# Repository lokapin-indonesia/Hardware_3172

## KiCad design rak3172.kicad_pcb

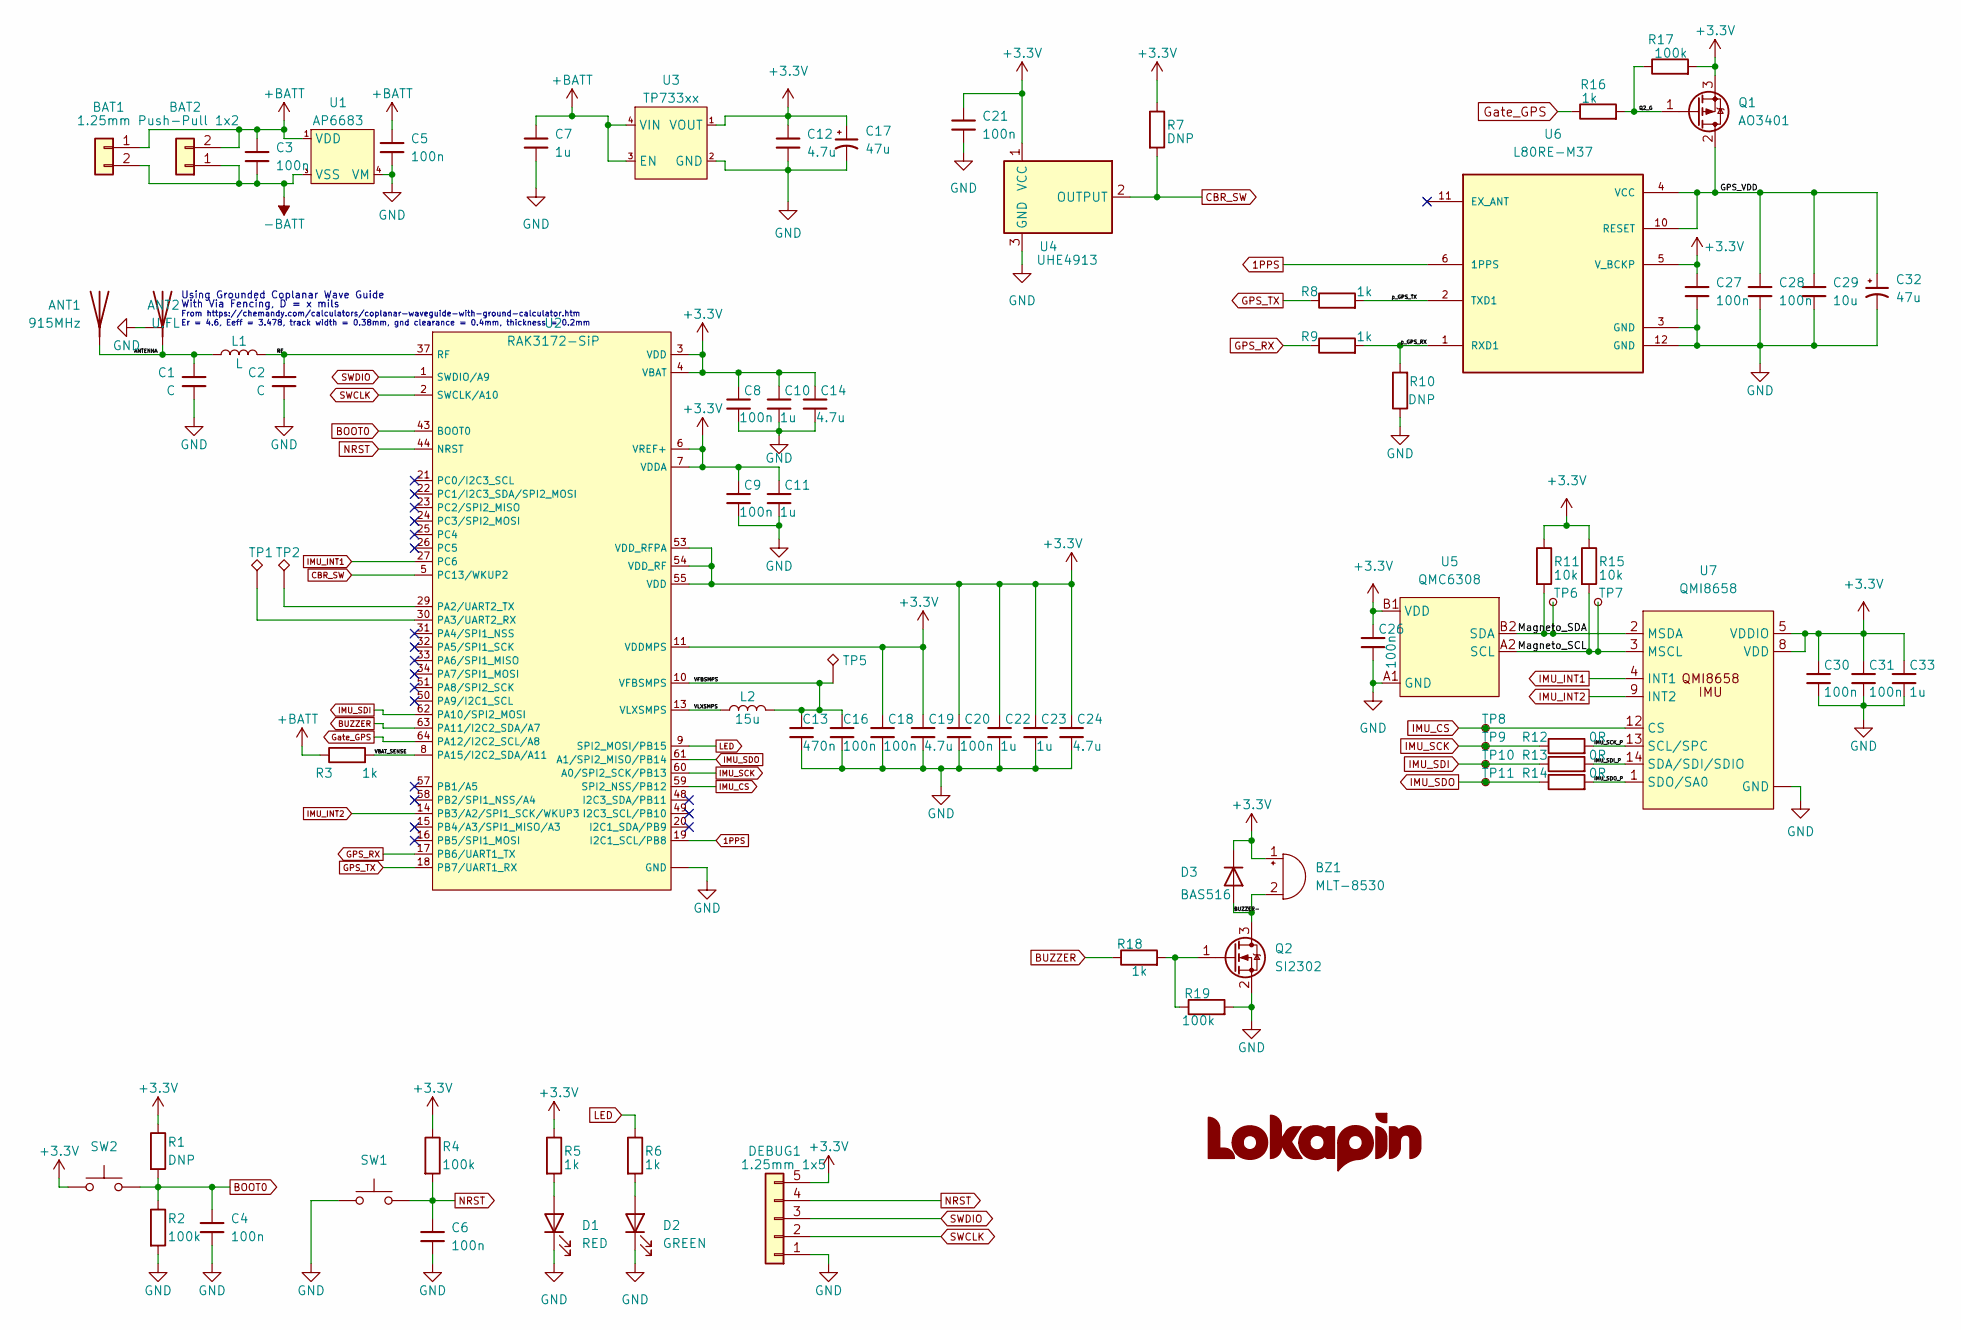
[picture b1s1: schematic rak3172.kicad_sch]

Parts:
ANT1: 915MHz; TestPoint_THTPad_D2.0mm_Drill1.0mm
ANT2: U.FL; U.FL_Hirose_U.FL-R-SMT-1_Vertical
BAT1, BAT2: 1.25mm Push-Pull 1x2; 1.25-2PWB DEALON
BZ1: MLT-8530; MagneticBuzzer_8530_SMD
C1, C2: C; C_0402_1005Metric
C3, C4, C5, C6, C8, C9, C16, C18, C20, C21, C26, C27, C28, C30, C31: 100n; C_0402_1005Metric
C7, C10, C11, C22, C23, C33: 1u; C_0402_1005Metric
C12, C14, C19, C24: 4.7u; C_0402_1005Metric
C13: 470n; C_0402_1005Metric
C17, C32: 47u; CP_EIA-3216-18_Kemet-A
C29: 10u; C_0402_1005Metric
D1: RED; LED_0603_1608Metric
D2: GREEN; LED_0603_1608Metric
D3: BAS516; D_SOD-523
DEBUG1: 1.25mm 1x5; Hirose_DF13-05P-1.25DSA_1x05_P1.25mm_Vertical
L1: L; L_0402_1005Metric
L2: 15u; L_0805_2012Metric
Q1: AO3401; SOT-23
Q2: SI2302; SOT-23
R1, R7, R10: DNP; R_0402_1005Metric
R2, R4, R17, R19: 100k; R_0402_1005Metric
R3, R5, R6, R8, R9, R16, R18: 1k; R_0402_1005Metric
R11, R15: 10k; R_0402_1005Metric
R12, R13, R14: 0R; R_0402_1005Metric
SW1, SW2: SW_Push; 5.2mm x 3.35mm Tactile Switch
TP1, TP2, TP5: TestPoint_Alt; TestPoint_Pad_D1.0mm
TP6, TP7, TP8, TP9, TP10, TP11: TestPoint_Small; TestPoint_Pad_D1.0mm
U1: AP6683; OnSemi_XDFN4-1EP_1.0x1.0mm_EP0.52x0.52mm
U2: RAK3172-SiP
U3: TP733xx; OnSemi_XDFN4-1EP_1.0x1.0mm_EP0.52x0.52mm
U4: UHE4913; SOT-23
U5: QMC6308
U6: L80RE-M37; XCVR_L80RE-M37
U7: QMI8658

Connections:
1PPS: U2.19 (I2C1_SCL/PB8), U6.6 (1PPS)
+3V3: BZ1.1 (-), C8.1, C9.1, C10.1, C11.1, C12.1, C14.1, C17.1, C18.1, C19.1, C20.1, C21.1, C22.1, C23.1, C24.1, C26.1, C27.1, C30.1, C31.1, C33.1, D3.1 (K), DEBUG1.5, Q1.3 (S), R1.1, R4.1, R5.1, R7.1, R11.1, R15.1, R17.2, SW2.1, U2.3 (VDD), U2.4 (VBAT), U2.6 (VREF+), U2.7 (VDDA), U2.11 (VDDMPS), U2.53 (VDD_RFPA), U2.54 (VDD_RF), U2.55 (VDD), U3.1 (VOUT), U4.1 (VCC), U5.B1 (VDD), U6.5 (V_BCKP), U7.5 (VDDIO), U7.8 (VDD)
+BATT: BAT1.1, BAT2.2, C3.1, C5.1, C7.1, R3.1, U1.1 (VDD), U3.3 (EN), U3.4 (VIN)
-BATT: BAT1.2, BAT2.1, C3.2, U1.2 (VSS), U1.3 (VSS)
/ANTENNA: ANT1.1 (A), ANT2.1 (A), C1.1, L1.2
/BUZZER-: BZ1.2 (+), D3.2 (A), Q2.3 (D)
/GPS_VDD: C28.1, C29.1, C32.1, Q1.2 (D), U6.4 (VCC), U6.10 (RESET)
/IMU_SCK_P: R12.2, U7.13 (SCL/SPC)
/IMU_SDI_P: R13.2, U7.14 (SDA/SDI/SDIO)
/IMU_SDO_P: R14.2, U7.1 (SDO/SA0)
/Magneto_SCL: R15.2, TP7.1, U5.A2 (SCL), U7.3 (MSCL)
/Magneto_SDA: R11.2, TP6.1, U5.B2 (SDA), U7.2 (MSDA)
/Q2_G: Q1.1 (G), R16.2, R17.1
/RF: C2.1, L1.1, U2.37 (RF)
/VBAT_SENSE: R3.2, U2.8 (PA15/I2C2_SDA/A11)
/VFBSMPS: C13.1, C16.1, L2.2, TP5.1, U2.10 (VFBSMPS)
/VLXSMPS: L2.1, U2.13 (VLXSMPS)
/p_GPS_RX: R9.2, R10.2, U6.1 (RXD1)
/p_GPS_TX: R8.2, U6.2 (TXD1)
BOOT0: C4.1, R1.2, R2.1, SW2.3, U2.43 (BOOT0)
BUZZER: R18.1, U2.63 (PA11/I2C2_SDA/A7)
CBR_SW: R7.2, U2.5 (PC13/WKUP2), U4.2 (OUTPUT)
GND: ANT2.2 (GND), C1.2, C2.2, C4.2, C5.2, C6.2, C7.2, C8.2, C9.2, C10.2, C11.2, C12.2, C13.2, C14.2, C16.2, C17.2, C18.2, C19.2, C20.2, C21.2, C22.2, C23.2, C24.2, C26.2, C27.2, C28.2, C29.2, C30.2, C31.2, C32.2, C33.2, D1.1 (K), D2.1 (K), DEBUG1.1, Q2.2 (S), R2.2, R10.1, R19.2, SW1.1, U1.4 (VM), U2.12 (GND), U2.28 (GND), U2.35 (GND), U2.36 (GND), U2.38 (GND), U2.39 (GND), U2.46 (GND), U2.47 (GND), U2.52 (GND), U2.56 (GND), U2.65 (GND), U2.66 (GND), U2.67 (GND), U2.68 (GND), U2.69 (GND), U2.70 (GND), U2.71 (GND), U2.72 (GND), U2.73 (GND), U3.2 (GND), U4.3 (GND), U5.A1 (GND), U6.3 (GND), U6.12 (GND), U7.6 (GND), U7.7 (GND)
GPS_RX: R9.1, U2.17 (PB6/UART1_TX)
GPS_TX: R8.1, U2.18 (PB7/UART1_RX)
Gate_GPS: R16.1, U2.64 (PA12/I2C2_SCL/A8)
IMU_CS: TP8.1, U2.59 (SPI2_NSS/PB12), U7.12 (CS)
IMU_INT1: U2.27 (PC6), U7.4 (INT1)
IMU_INT2: U2.14 (PB3/A2/SPI1_SCK/WKUP3), U7.9 (INT2)
IMU_SCK: R12.1, TP9.1, U2.60 (A0/SPI2_SCK/PB13)
IMU_SDI: R13.1, TP10.1, U2.62 (PA10/SPI2_MOSI)
IMU_SDO: R14.1, TP11.1, U2.61 (A1/SPI2_MISO/PB14)
LED: R6.1, U2.9 (SPI2_MOSI/PB15)
NRST: C6.1, DEBUG1.4, R4.2, SW1.3, U2.44 (NRST)
unnamed: D1.2 (A), R5.2
unnamed: D2.2 (A), R6.2
unnamed: Q2.1 (G), R18.2, R19.1
unnamed: TP1.1, U2.30 (PA3/UART2_RX)
unnamed: TP2.1, U2.29 (PA2/UART2_TX)
SWCLK: DEBUG1.2, U2.2 (SWCLK/A10)
SWDIO: DEBUG1.3, U2.1 (SWDIO/A9)

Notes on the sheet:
From https://chemandy.com/calculators/coplanar-waveguide-with-ground-calculator.htm Er = 4.6, Eeff = 3.478, track width = 0.38mm, gnd clearance = 0.4mm, thickness = 0.2mm
Using Grounded Coplanar Wave Guide
With Via Fencing, D = x mils

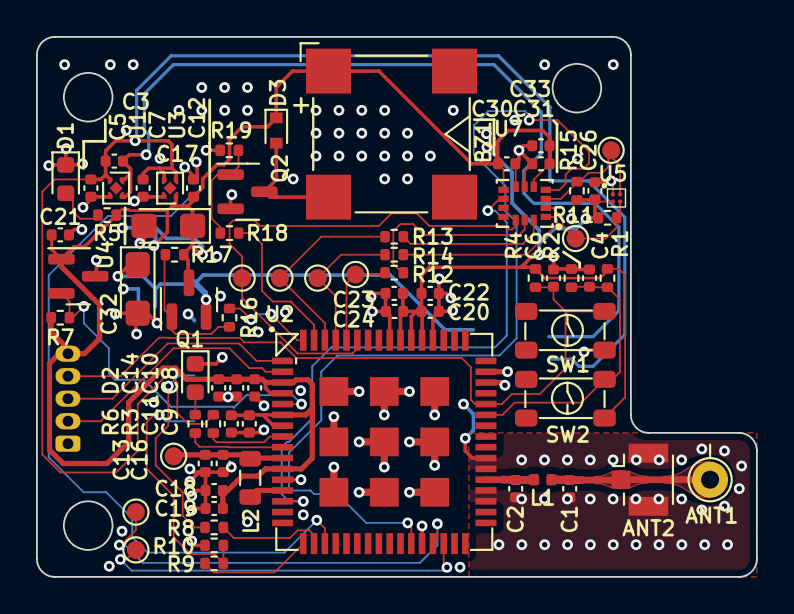
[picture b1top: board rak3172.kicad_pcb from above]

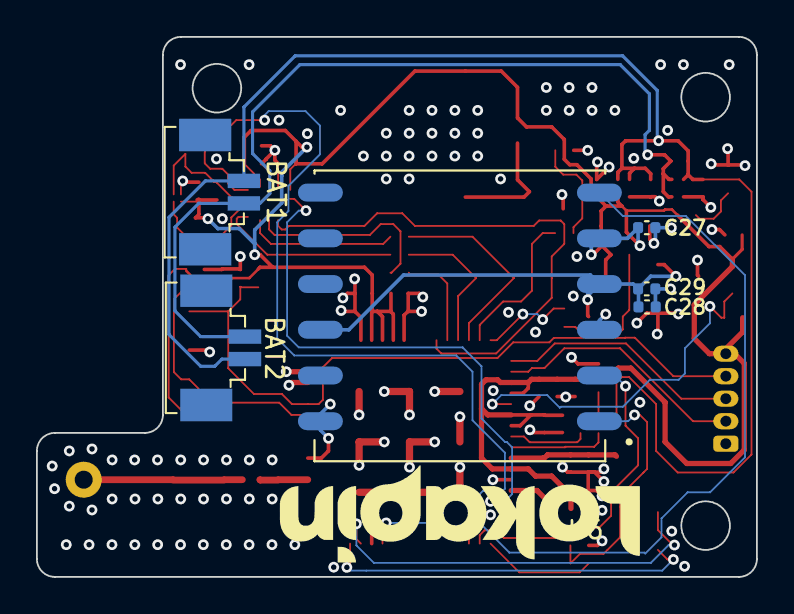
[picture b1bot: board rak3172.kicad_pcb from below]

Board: 4 copper layers, 40.0 x 30.0 mm, 81 parts (6 on the bottom side), 41 nets.

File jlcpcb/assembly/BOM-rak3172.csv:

Comment,Designator,Footprint,LCSC
100k,"R17,R19,R2,R4",R_0402_1005Metric,C106234
470n,C13,C_0402_1005Metric,C106255
47u,"C17,C32",CP_EIA-3216-18_Kemet-A,C139817
1k,"R16,R18,R3,R5,R6,R8,R9",R_0402_1005Metric,C140196
10u,C29,C_0402_1005Metric,C15525
1u,"C10,C11,C22,C23,C33,C7",C_0402_1005Metric,C15684
AP6683,U1,OnSemi_XDFN4-1EP_1.0x1.0mm_EP0.52x0.52mm,C2843221
SW_Push,"SW1,SW2",5.2mm x 3.35mm Tactile Switch,C2888427
SI2302,Q2,SOT-23,C2891732
1.25mm Push-Pull 1x2,"BAT1,BAT2",1.25-2PWB DEALON,C2905009
L,"L1,R12,R13,R14",L_0402_1005Metric,C2906877
TP733xx,U3,OnSemi_XDFN4-1EP_1.0x1.0mm_EP0.52x0.52mm,C2923371
QMI8658,U7,QMI8658,C3021082
L80RE-M37,U6,XCVR_L80RE-M37,C3029061
4.7u,"C12,C14,C19,C24",C_0402_1005Metric,C307423
AO3401,Q1,SOT-23,C347476
QMC6308,U5,QMC6308,C462705
15u,L2,L_0805_2012Metric,C486333
U.FL,ANT2,U.FL_Hirose_U.FL-R-SMT-1_Vertical,C5137195
100n,"C16,C18,C20,C21,C26,C27,C28,C3,C30,C31,C4,C5,C6,C8,C9",C_0402_1005Metric,C541406
10k,"R11,R15",R_0402_1005Metric,C60489
BAS516,D3,D_SOD-523,C699078
915MHz,ANT1,TestPoint_THTPad_D2.0mm_Drill1.0mm,C726086
UHE4913,U4,SOT-23,C86815
MLT-8530,BZ1,MagneticBuzzer_8530_SMD,C94599
RED,D1,LED_0603_1608Metric,C965799
GREEN,D2,LED_0603_1608Metric,C965804
RAK3172-SiP,U2,RAK3172-SiP,

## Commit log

2022-09-23 added rak3172 lib
2022-09-25 routing done, untidy
2022-10-01 Q, ANT, D name deleted
2022-10-06 Added 3D Models (-Antenna) Added Manufacturing File (BOM/POS/Gerber) Tidied up silkscreen placement Added via stitching Added via fencing for GCPW Changed bat connector position and package (to SMD)
2022-12-10 urip
